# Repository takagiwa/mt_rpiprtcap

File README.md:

# mt_rpiprtcap

Capture print data via parallel port on PC and some measurement equipments.

Main purpose is for taking hardcopy on elder measurement equipments that don't have USB or modern hardcopy device.

The PCB design file for KiCAD is in "board" directory.

The software code depends on pigpiod is in "software_rpi" directory.

you can build software as following (comes from pigpio)

gcc -Wall -pthread -o prt prt.cpp -lpigpiod_if2 -lrt

I have tested on Raspbian GNU/Linux 10 (buster), gcc 8.3.0, pigpio 78 (get_pigpio_version reported) and Raspberry Pi 4B 2GB.

The software still have some huge bugs.

* failed to capture first byte
* sometime failed to capture data (3 or 4 characters in 10MB).
* too slow (almost 1KB/sec)

There are no interpreters that convert from parallel port data to picture yet.

How to use

connect all devices.

power-on all devices.

start software_rpi/prt executable

start print on PC or equipment

when it seems ended, Ctrl-C on prt executable

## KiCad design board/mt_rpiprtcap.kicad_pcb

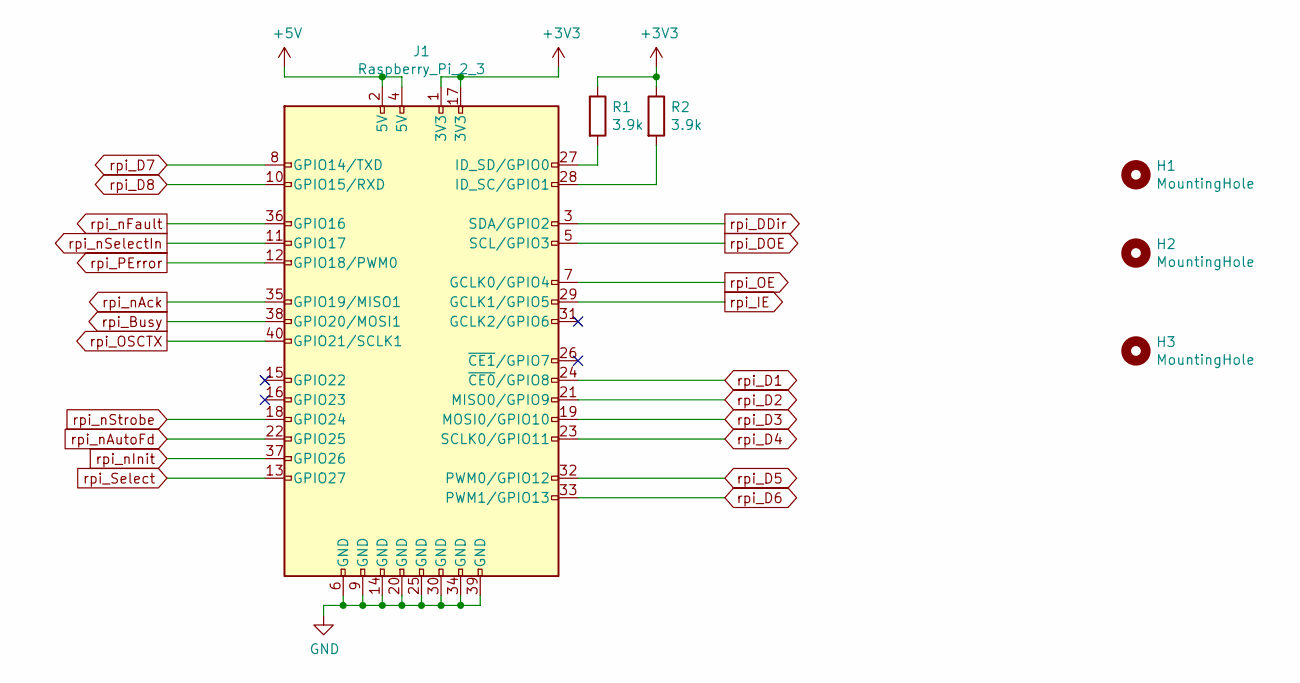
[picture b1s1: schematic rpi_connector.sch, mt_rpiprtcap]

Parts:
H1, H2, H3: MountingHole; MountingHole_2.7mm_M2.5
J1: Raspberry_Pi_2_3; Pin_Header_Straight_2x20_Pitch2.54mm
R1, R2: 3.9k; R_0805_HandSoldering

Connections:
+3V3: J1.1 (3V3), J1.17 (3V3), R1.1, R2.1; also elsewhere on the board
+5V: J1.2 (5V), J1.4 (5V); also elsewhere on the board
GND: J1.6 (GND), J1.9 (GND), J1.14 (GND), J1.20 (GND), J1.25 (GND), J1.30 (GND), J1.34 (GND), J1.39 (GND); also elsewhere on the board
unnamed: J1.27 (ID_SD/GPIO0), R1.2
unnamed: J1.28 (ID_SC/GPIO1), R2.2
rpi_Busy: J1.38 (GPIO20/MOSI1); also elsewhere on the board
rpi_D1: J1.24 (~CE0~/GPIO8); also elsewhere on the board
rpi_D2: J1.21 (MISO0/GPIO9); also elsewhere on the board
rpi_D3: J1.19 (MOSI0/GPIO10); also elsewhere on the board
rpi_D4: J1.23 (SCLK0/GPIO11); also elsewhere on the board
rpi_D5: J1.32 (PWM0/GPIO12); also elsewhere on the board
rpi_D6: J1.33 (PWM1/GPIO13); also elsewhere on the board
rpi_D7: J1.8 (GPIO14/TXD); also elsewhere on the board
rpi_D8: J1.10 (GPIO15/RXD); also elsewhere on the board
rpi_DDir: J1.3 (SDA/GPIO2); also elsewhere on the board
rpi_DOE: J1.5 (SCL/GPIO3); also elsewhere on the board
rpi_IE: J1.29 (GCLK1/GPIO5); also elsewhere on the board
rpi_OE: J1.7 (GCLK0/GPIO4); also elsewhere on the board
rpi_OSCTX: J1.40 (GPIO21/SCLK1); also elsewhere on the board
rpi_PError: J1.12 (GPIO18/PWM0); also elsewhere on the board
rpi_Select: J1.13 (GPIO27); also elsewhere on the board
rpi_nAck: J1.35 (GPIO19/MISO1); also elsewhere on the board
rpi_nAutoFd: J1.22 (GPIO25); also elsewhere on the board
rpi_nFault: J1.36 (GPIO16); also elsewhere on the board
rpi_nInit: J1.37 (GPIO26); also elsewhere on the board
rpi_nSelectIn: J1.11 (GPIO17); also elsewhere on the board
rpi_nStrobe: J1.18 (GPIO24); also elsewhere on the board

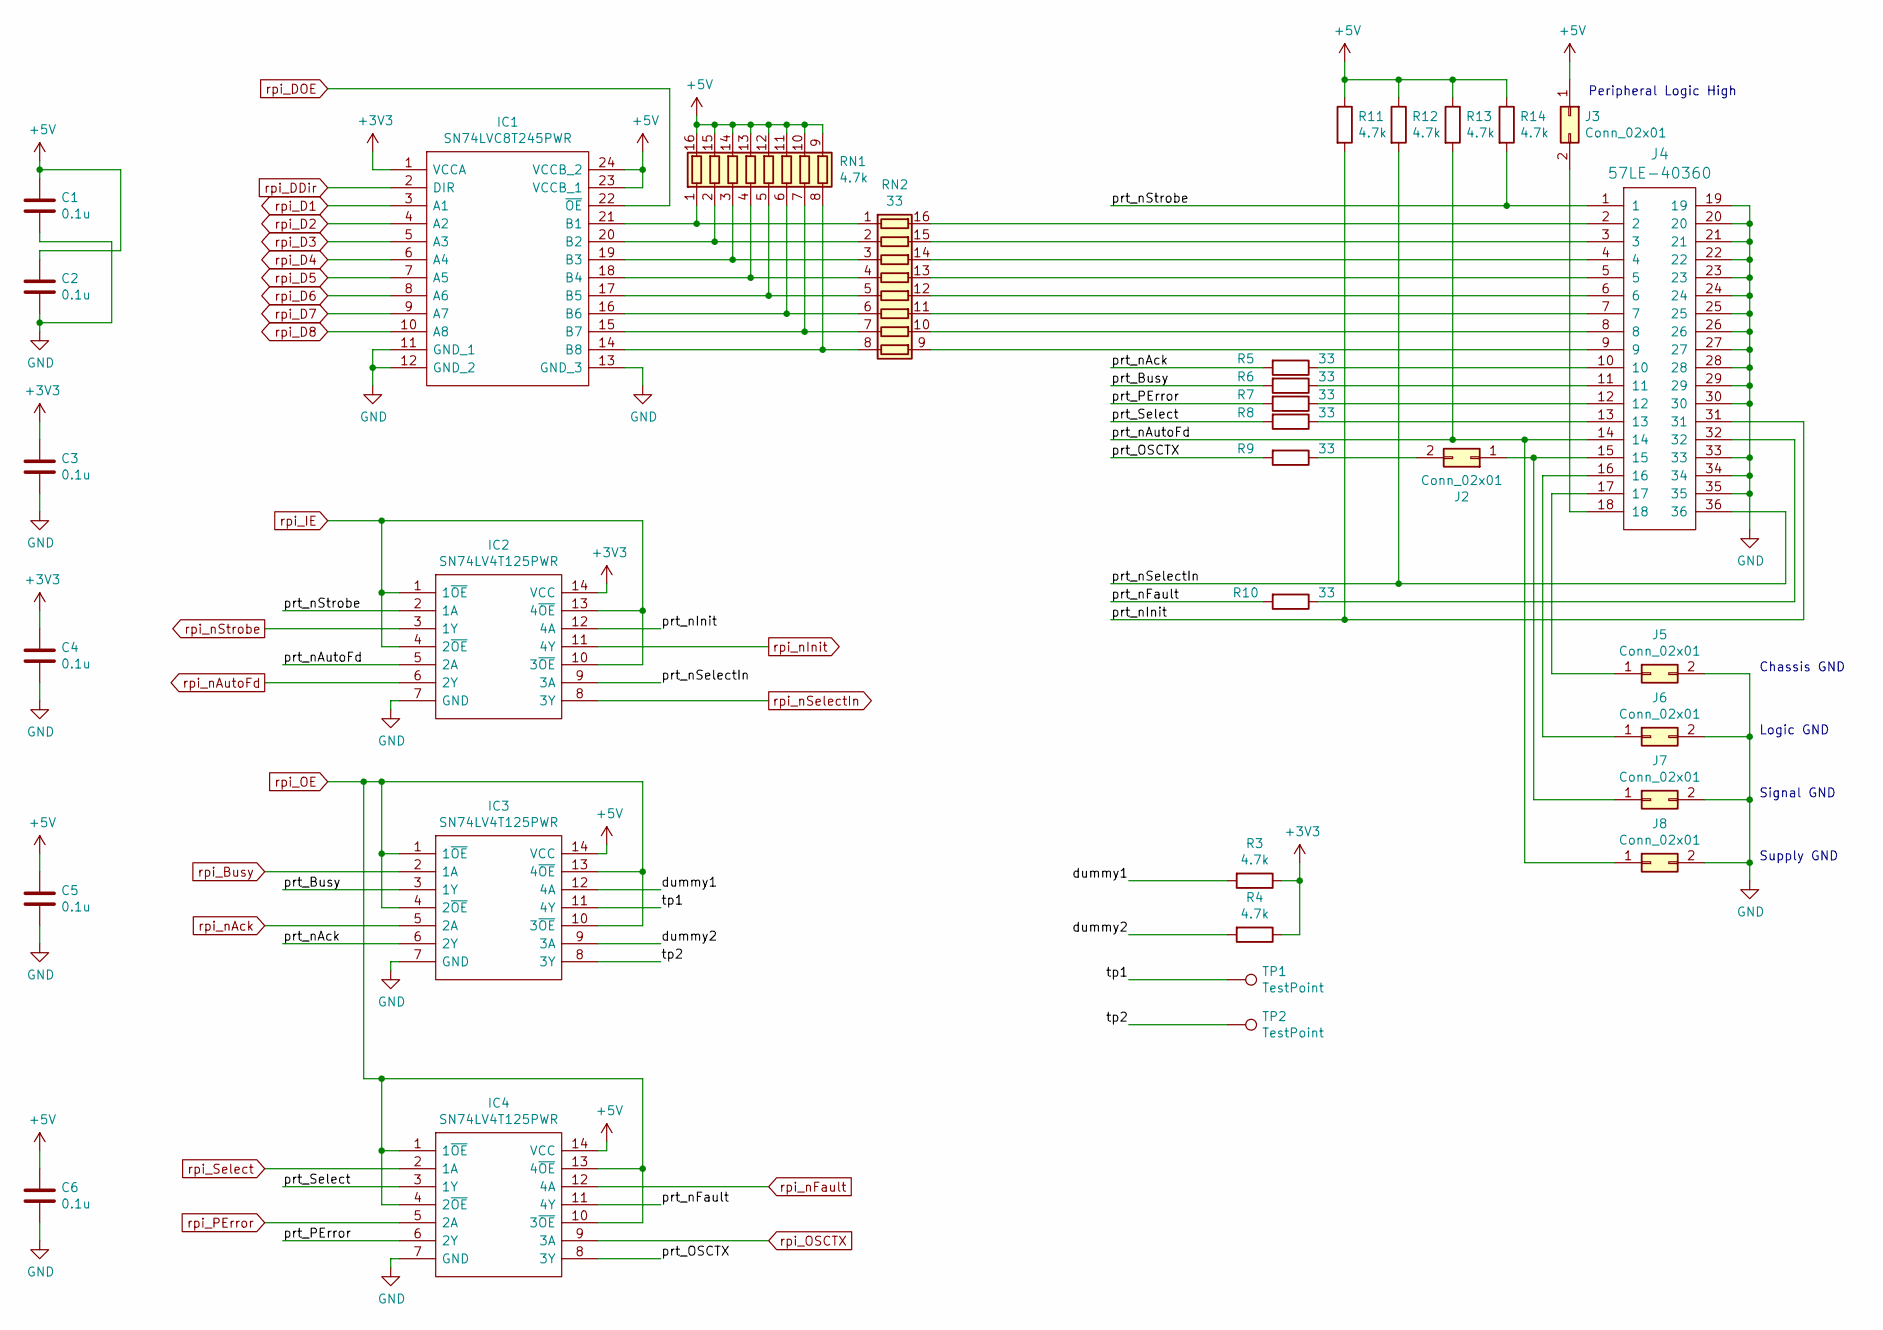
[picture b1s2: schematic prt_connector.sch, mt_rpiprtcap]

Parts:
C1, C2, C3, C4, C5, C6: 0.1u; C_0805_HandSoldering
IC1: SN74LVC8T245PWR; SOP65P640X120-24N; Mouser Part Number 595-SN74LVC8T245PWR
IC2, IC3, IC4: SN74LV4T125PWR; SOP65P640X120-14N; Mouser Part Number 595-SN74LV4T125PWR
J2, J3, J5, J6, J7, J8: Conn_02x01; Pin_Header_Straight_2x01_Pitch2.54mm
J4: 57LE-40360
R3, R4, R11, R12, R13, R14: 4.7k; R_0805_HandSoldering
R5, R6, R7, R8, R9, R10: 33; R_0805_HandSoldering
RN1: 4.7k; R_Array_Convex_8x0602
RN2: 33; R_Array_Convex_8x0602
TP1, TP2: TestPoint; Measurement_Point_Round-SMD-Pad_Small

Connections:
+3V3: C3.1, C4.1, IC1.1 (VCCA), IC2.14 (VCC), R3.1, R4.1; also elsewhere on the board
+5V: C1.1, C2.1, C5.1, C6.1, IC1.23 (VCCB_1), IC1.24 (VCCB_2), IC3.14 (VCC), IC4.14 (VCC), J3.1, R11.1, R12.1, R13.1, R14.1, RN1.9 (R8.2), RN1.10 (R7.2), RN1.11 (R6.2), RN1.12 (R5.2), RN1.13 (R4.2), RN1.14 (R3.2), RN1.15 (R2.2), RN1.16 (R1.2); also elsewhere on the board
/prt_connector/dummy1: IC3.12 (4A), R3.2
/prt_connector/dummy2: IC3.9 (3A), R4.2
/prt_connector/prt_Busy: IC3.3 (1Y), R6.2
/prt_connector/prt_OSCTX: IC4.8 (3Y), R9.2
/prt_connector/prt_PError: IC4.6 (2Y), R7.2
/prt_connector/prt_Select: IC4.3 (1Y), R8.2
/prt_connector/prt_nAck: IC3.6 (2Y), R5.2
/prt_connector/prt_nAutoFd: IC2.5 (2A), J4.14, J8.1, R13.2
/prt_connector/prt_nFault: IC4.11 (4Y), R10.2
/prt_connector/prt_nInit: IC2.12 (4A), J4.31, R11.2
/prt_connector/prt_nSelectIn: IC2.9 (3A), J4.36, R12.2
/prt_connector/prt_nStrobe: IC2.2 (1A), J4.1, R14.2
/prt_connector/tp1: IC3.11 (4Y), TP1.1
/prt_connector/tp2: IC3.8 (3Y), TP2.1
GND: C1.2, C2.2, C3.2, C4.2, C5.2, C6.2, IC1.11 (GND_1), IC1.12 (GND_2), IC1.13 (GND_3), IC2.7 (GND), IC3.7 (GND), IC4.7 (GND), J4.19, J4.20, J4.21, J4.22, J4.23, J4.24, J4.25, J4.26, J4.27, J4.28, J4.29, J4.30, J4.33, J4.34, J4.35, J5.2, J6.2, J7.2, J8.2; also elsewhere on the board
unnamed: IC1.14 (B8), RN1.8 (R8.1), RN2.8 (R8.1)
unnamed: IC1.15 (B7), RN1.7 (R7.1), RN2.7 (R7.1)
unnamed: IC1.16 (B6), RN1.6 (R6.1), RN2.6 (R6.1)
unnamed: IC1.17 (B5), RN1.5 (R5.1), RN2.5 (R5.1)
unnamed: IC1.18 (B4), RN1.4 (R4.1), RN2.4 (R4.1)
unnamed: IC1.19 (B3), RN1.3 (R3.1), RN2.3 (R3.1)
unnamed: IC1.20 (B2), RN1.2 (R2.1), RN2.2 (R2.1)
unnamed: IC1.21 (B1), RN1.1 (R1.1), RN2.1 (R1.1)
unnamed: J2.1, J4.15, J7.1
unnamed: J2.2, R9.1
unnamed: J3.2, J4.18
unnamed: J4.2, RN2.16 (R1.2)
unnamed: J4.3, RN2.15 (R2.2)
unnamed: J4.4, RN2.14 (R3.2)
unnamed: J4.5, RN2.13 (R4.2)
unnamed: J4.6, RN2.12 (R5.2)
unnamed: J4.7, RN2.11 (R6.2)
unnamed: J4.8, RN2.10 (R7.2)
unnamed: J4.9, RN2.9 (R8.2)
unnamed: J4.10, R5.1
unnamed: J4.11, R6.1
unnamed: J4.12, R7.1
unnamed: J4.13, R8.1
unnamed: J4.16, J6.1
unnamed: J4.17, J5.1
unnamed: J4.32, R10.1
rpi_Busy: IC3.2 (1A); also elsewhere on the board
rpi_D1: IC1.3 (A1); also elsewhere on the board
rpi_D2: IC1.4 (A2); also elsewhere on the board
rpi_D3: IC1.5 (A3); also elsewhere on the board
rpi_D4: IC1.6 (A4); also elsewhere on the board
rpi_D5: IC1.7 (A5); also elsewhere on the board
rpi_D6: IC1.8 (A6); also elsewhere on the board
rpi_D7: IC1.9 (A7); also elsewhere on the board
rpi_D8: IC1.10 (A8); also elsewhere on the board
rpi_DDir: IC1.2 (DIR); also elsewhere on the board
rpi_DOE: IC1.22 (~OE); also elsewhere on the board
rpi_IE: IC2.1 (1~OE), IC2.4 (2~OE), IC2.10 (3~OE), IC2.13 (4~OE); also elsewhere on the board
rpi_OE: IC3.1 (1~OE), IC3.4 (2~OE), IC3.10 (3~OE), IC3.13 (4~OE), IC4.1 (1~OE), IC4.4 (2~OE), IC4.10 (3~OE), IC4.13 (4~OE); also elsewhere on the board
rpi_OSCTX: IC4.9 (3A); also elsewhere on the board
rpi_PError: IC4.5 (2A); also elsewhere on the board
rpi_Select: IC4.2 (1A); also elsewhere on the board
rpi_nAck: IC3.5 (2A); also elsewhere on the board
rpi_nAutoFd: IC2.6 (2Y); also elsewhere on the board
rpi_nFault: IC4.12 (4A); also elsewhere on the board
rpi_nInit: IC2.11 (4Y); also elsewhere on the board
rpi_nSelectIn: IC2.8 (3Y); also elsewhere on the board
rpi_nStrobe: IC2.3 (1Y); also elsewhere on the board

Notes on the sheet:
Peripheral Logic High
Chassis GND
Logic GND
Signal GND
Supply GND

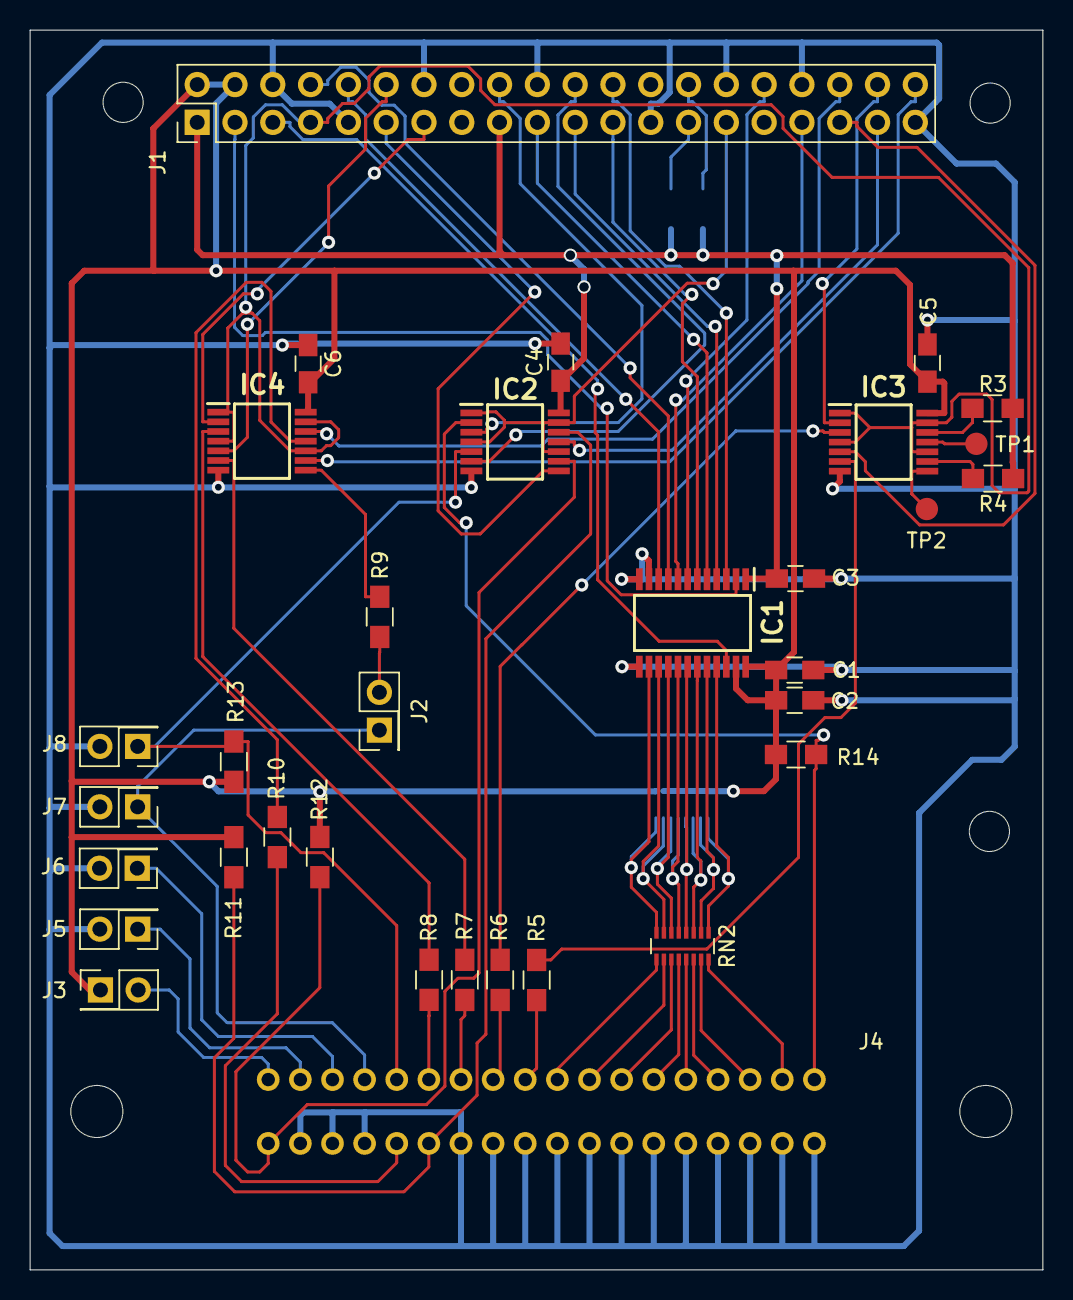
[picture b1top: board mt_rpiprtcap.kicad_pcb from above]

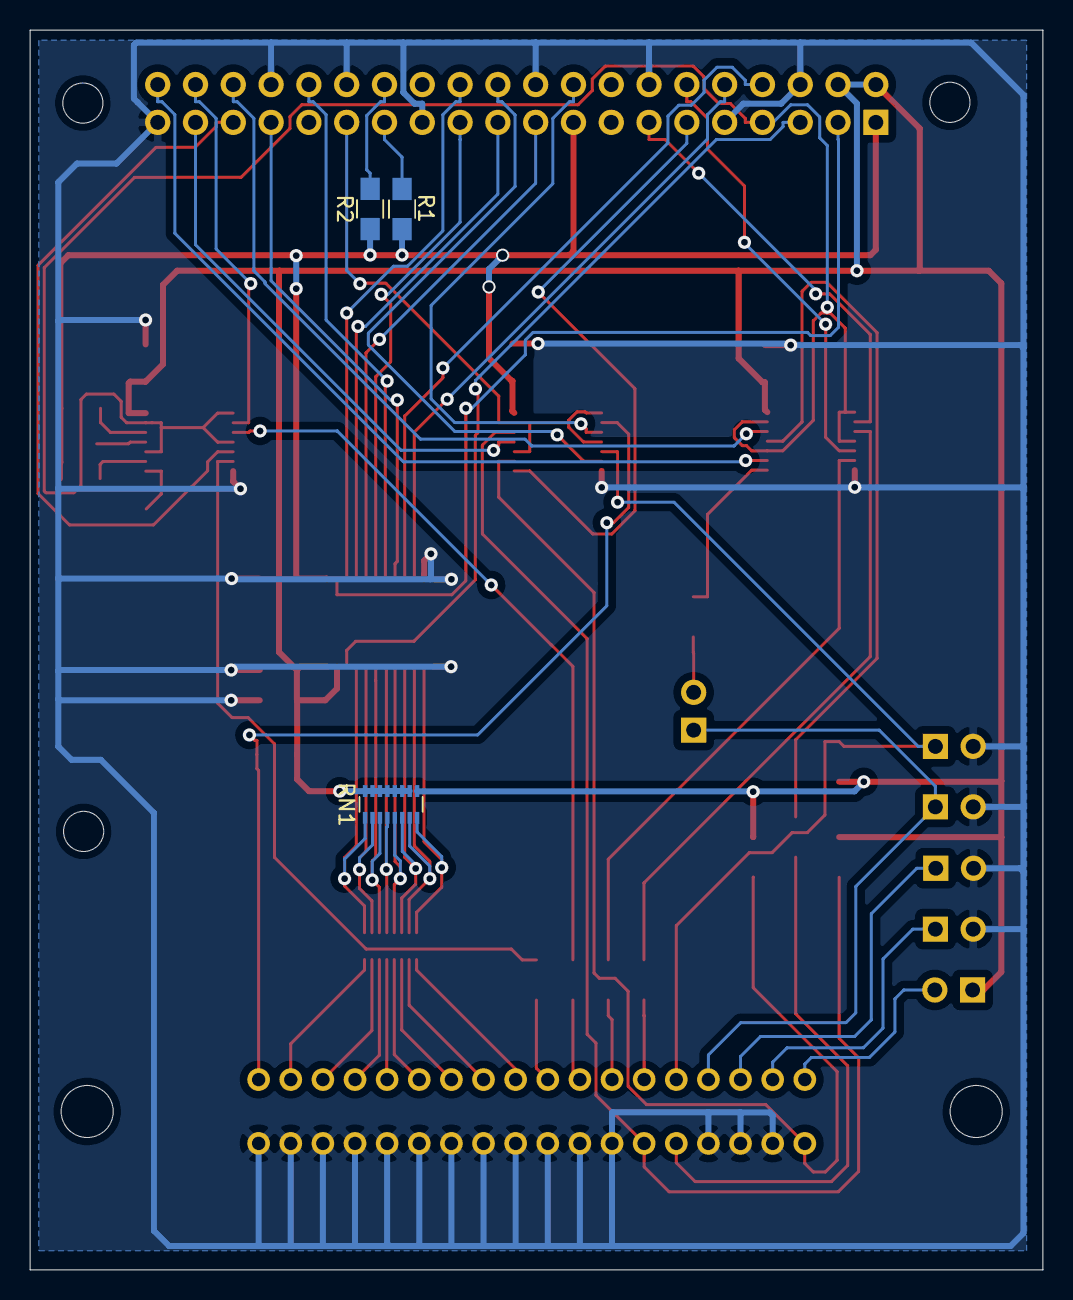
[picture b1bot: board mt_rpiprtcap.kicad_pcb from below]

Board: 2 copper layers, 68.1 x 83.3 mm, 39 parts (3 on the bottom side), 67 nets.

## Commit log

2020-09-28 first proto type board
2020-10-04 Update sheet information.
2021-01-10 add first software. there are some data corrupt.
2021-01-10 remove old codes

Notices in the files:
board/prt_connector.sch:
GPLv2
